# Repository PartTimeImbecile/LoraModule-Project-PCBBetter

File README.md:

# LoraModule-Project-PCBBetter
A better pcb I created for combining an ESP32S3 Supermini and a wide variety of Lora SMD chips such as the RA-01SH

This can technically be made on a single layer board but should be done on a dual layer for better emf protection and grounding

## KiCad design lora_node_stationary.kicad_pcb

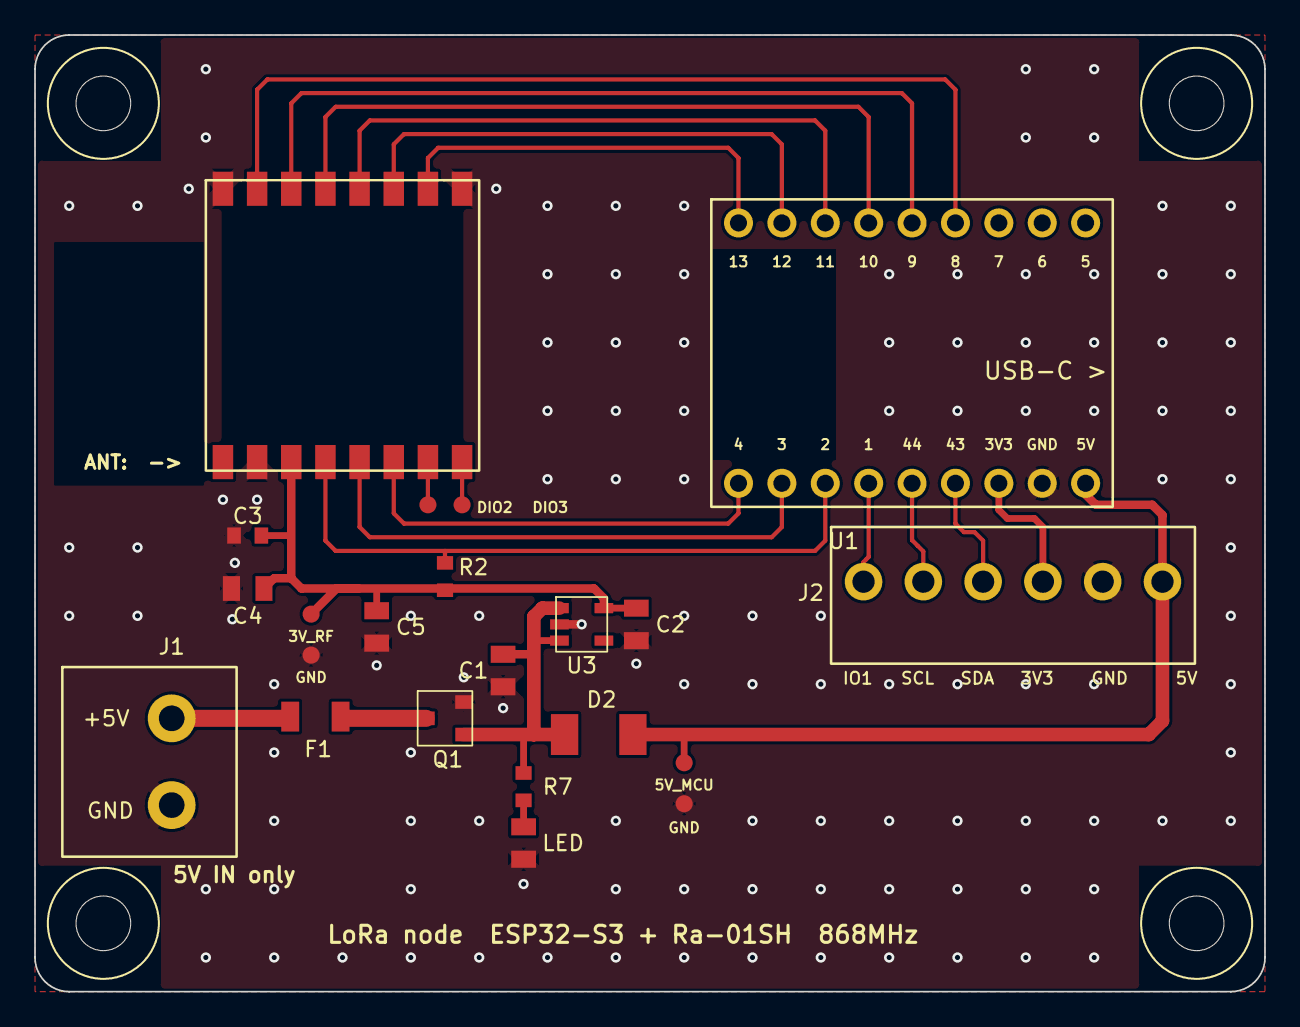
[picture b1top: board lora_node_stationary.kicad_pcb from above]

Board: 2 copper layers, 72.0 x 56.0 mm, 26 parts (0 on the bottom side), 22 nets.

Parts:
C1, C2, C4: 10uF; C_0805
C3: 100nF; C_0603
C5: 22uF bulk; C_0805
D2: SS14 Schottky; D_SMA
F1: PTC 1.1A 1206; Fuse_1206
H1, H2, H3, H4: M3; MountingHole_3.2mm_M3
J1: Screw terminal 5.08mm 2P (5V IN); TerminalBlock_5.08mm_2P
J2: Screw terminal 3.5mm 6P (sensors); TerminalBlock_3.5mm_6P
LED: LED green; LED_0805
Q1: AO3401A (P-MOS rev. protect); SOT-23_rot
R2: 10k RESET pull-up; R_0603
R7: 1k; R_0603
TP1: TP_DIO2; TestPoint_D1.0
TP2: TP_DIO3; TestPoint_D1.0
TP3, TP3#2: TP_5V_MCU; TestPoint_D1.0
TP4, TP4#2: TP_GND; TestPoint_D1.0
U1: ESP32-S3 SuperMini; SuperMini_2x9_P2.54_socket
U2: Ai-Thinker Ra-01SH (SX1262); Ra-01SH_SMD16_U.FL
U3: Torex XC6220B331MR-G; SOT-23-5

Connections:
3V3_MCU: J2.4, U1.A3
3V3_RF: C2.1, C3.1, C4.1, C5.1, R2.2, TP3.1, U2.3, U3.5
5V: C1.1, D2.1, Q1.2, R7.1, U3.1, U3.3
5V_F: F1.2, Q1.3
5V_IN: F1.1, J1.1
5V_MCU: D2.2, J2.6, TP3#2.1, U1.A1
BUSY: U1.B9, U2.10
DIO1: U1.A9, U2.6
DIO2: TP1.1, U2.7
DIO3: TP2.1, U2.8
GND: C1.2, C2.2, C3.2, C4.2, C5.2, J1.2, J2.5, LED.2, Q1.1, TP4.1, TP4#2.1, U1.A2, U2.2, U2.9, U2.16, U3.2
IO1_SENSE: J2.1, U1.A6
LED_A: LED.1, R7.2
MISO: U1.B6, U2.13
MOSI: U1.B5, U2.14
NSS: U1.B4, U2.15
RESET: R2.1, U1.A7, U2.4
RXEN: U1.B8, U2.11
SCK: U1.B7, U2.12
SCL: J2.2, U1.A5
SDA: J2.3, U1.A4
TXEN: U1.A8, U2.5
